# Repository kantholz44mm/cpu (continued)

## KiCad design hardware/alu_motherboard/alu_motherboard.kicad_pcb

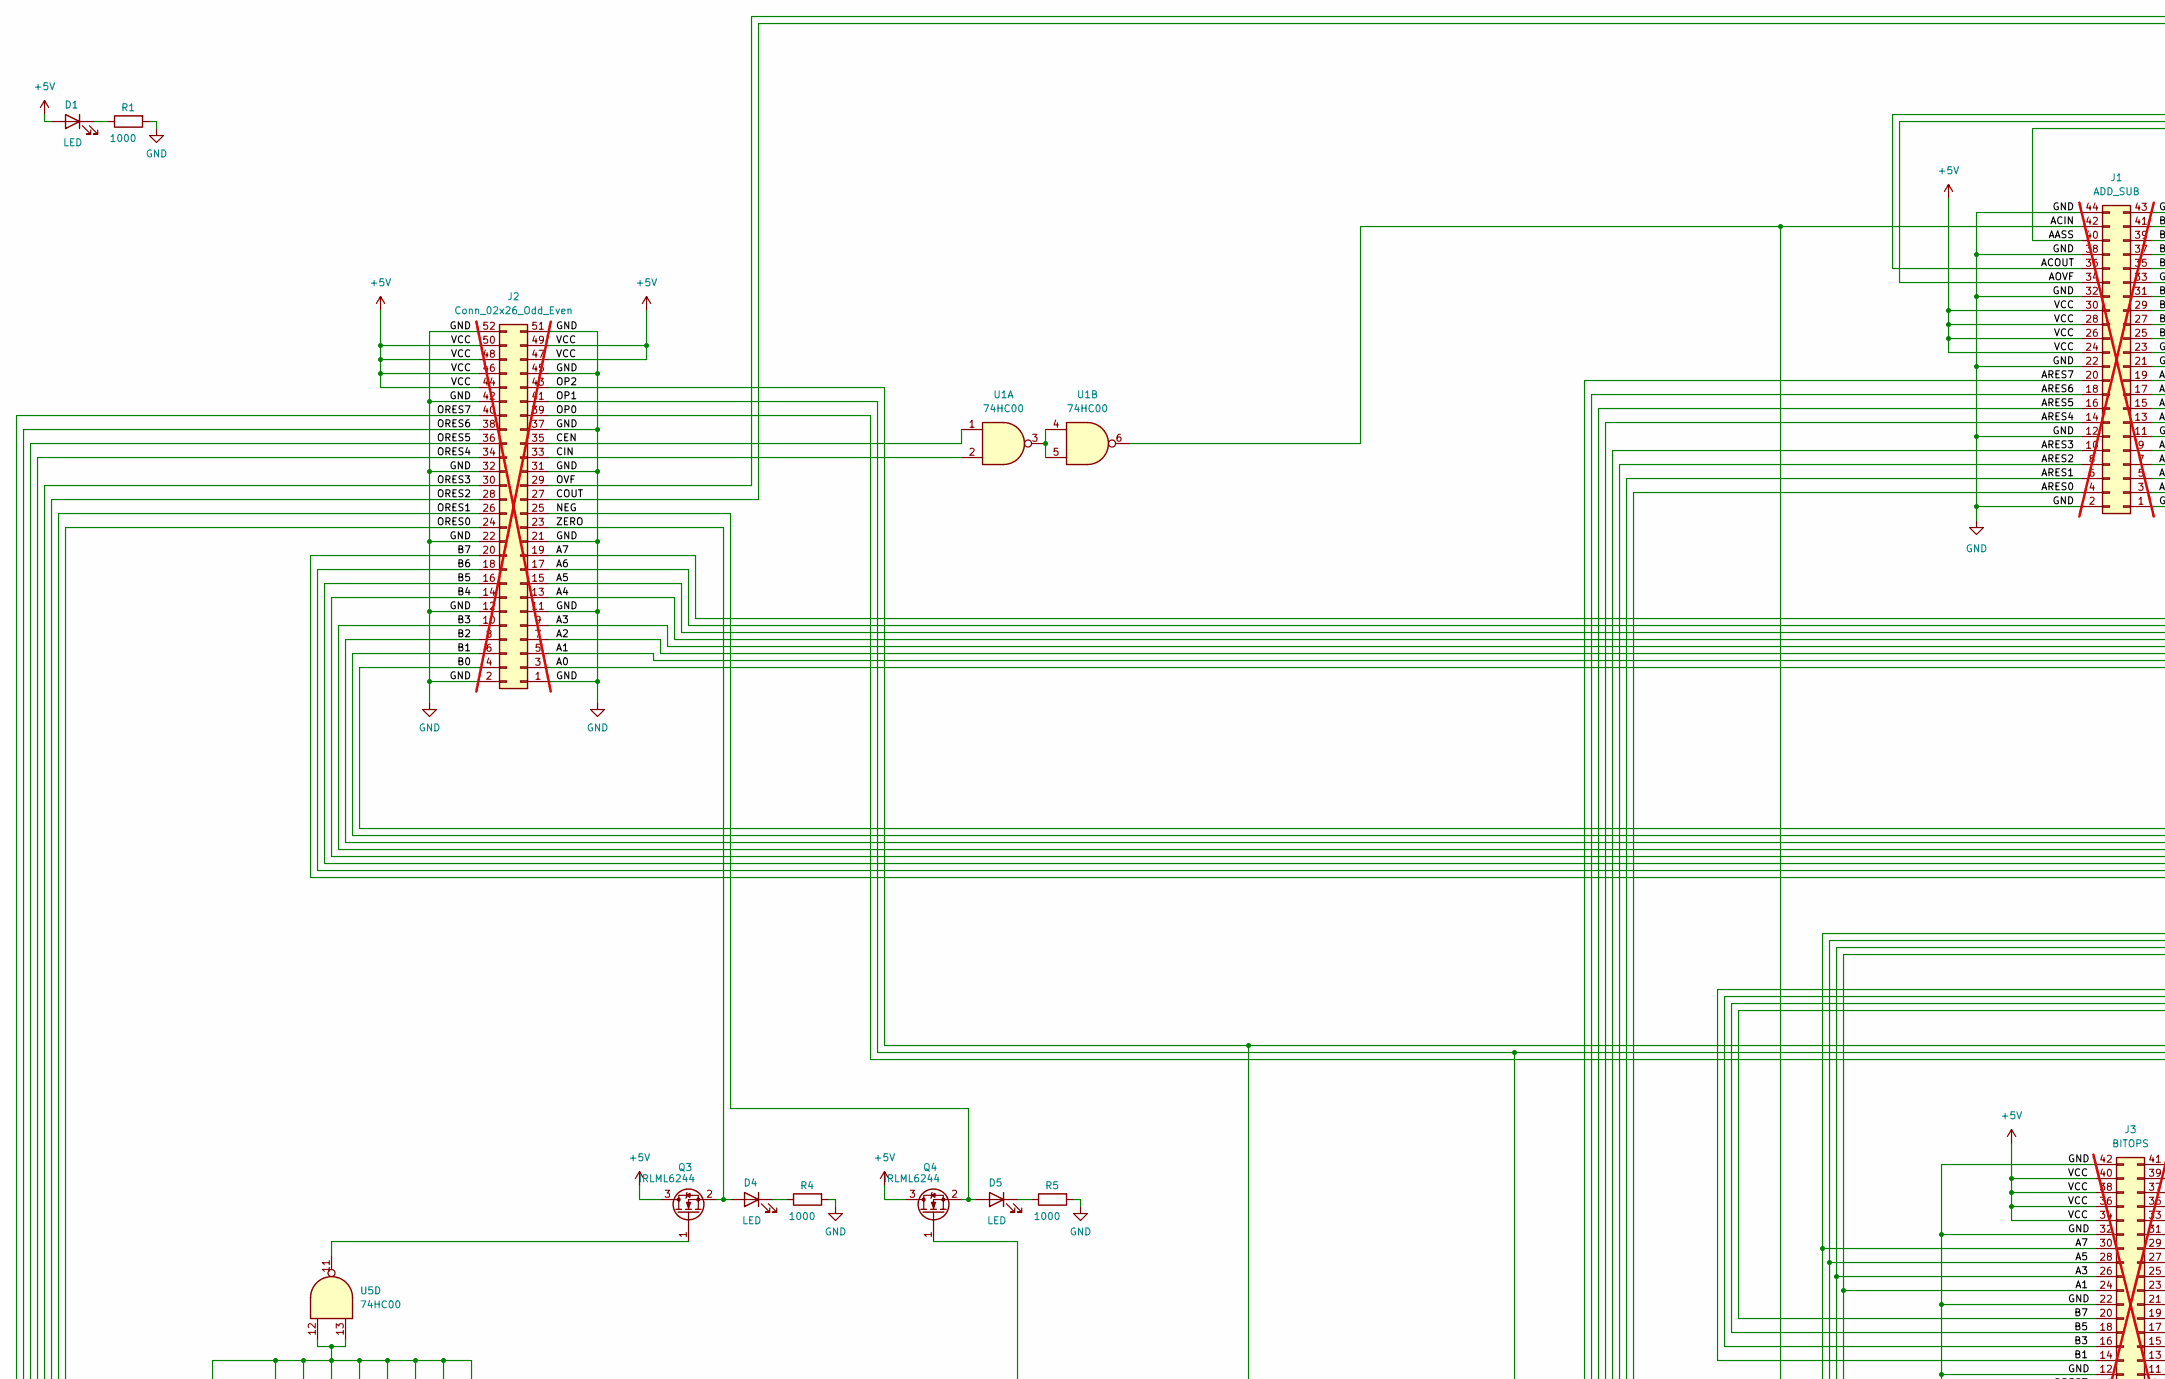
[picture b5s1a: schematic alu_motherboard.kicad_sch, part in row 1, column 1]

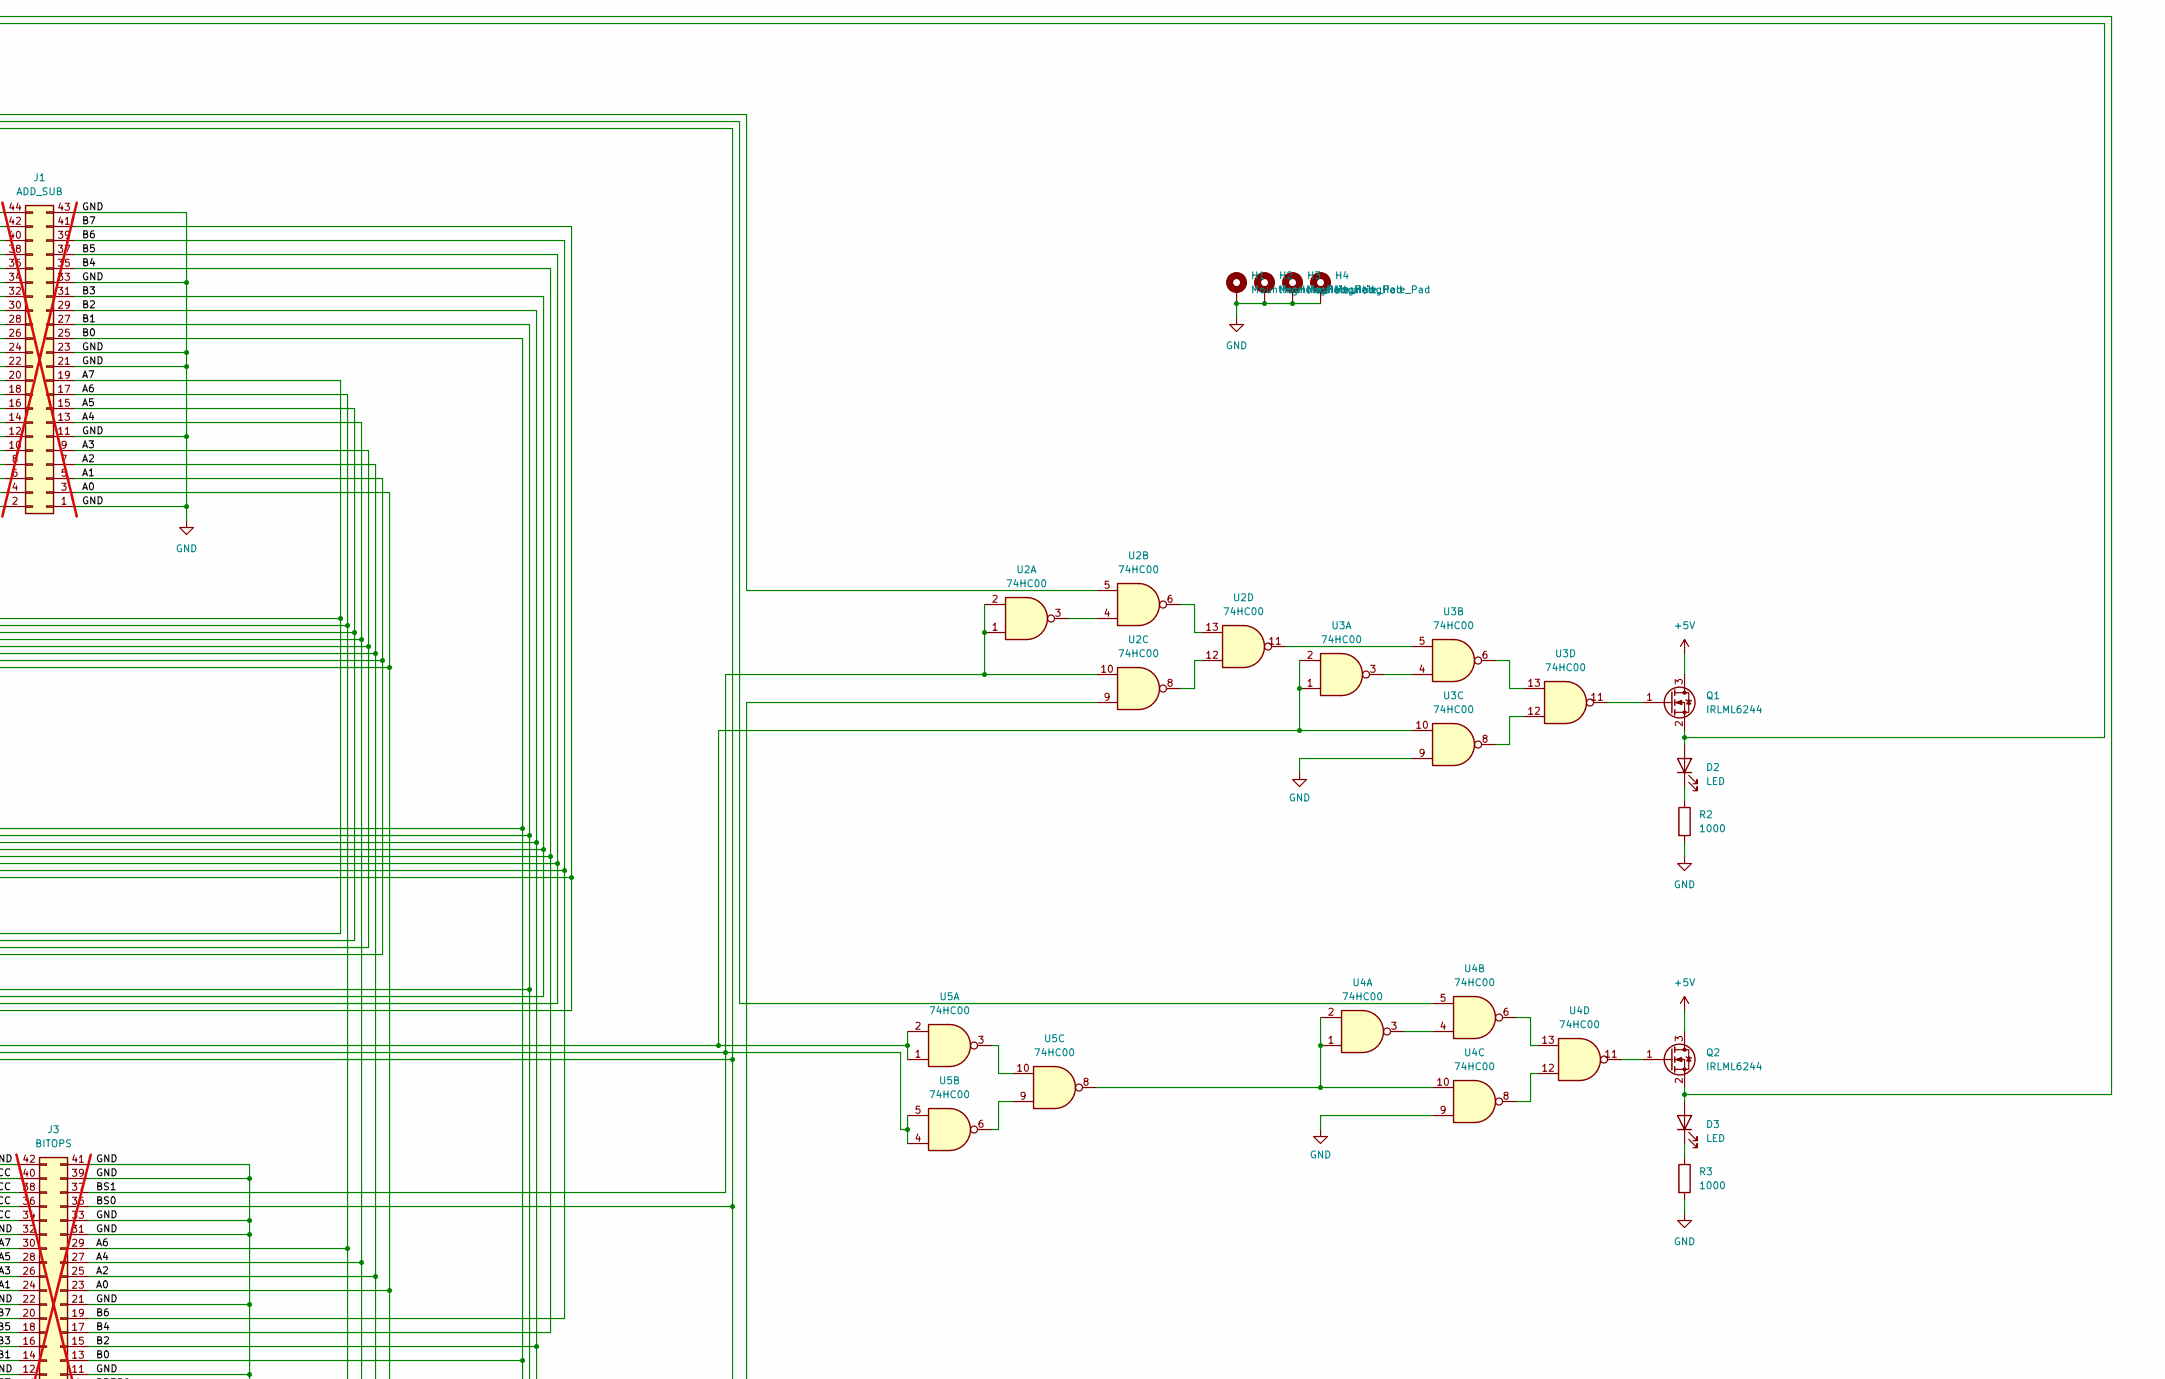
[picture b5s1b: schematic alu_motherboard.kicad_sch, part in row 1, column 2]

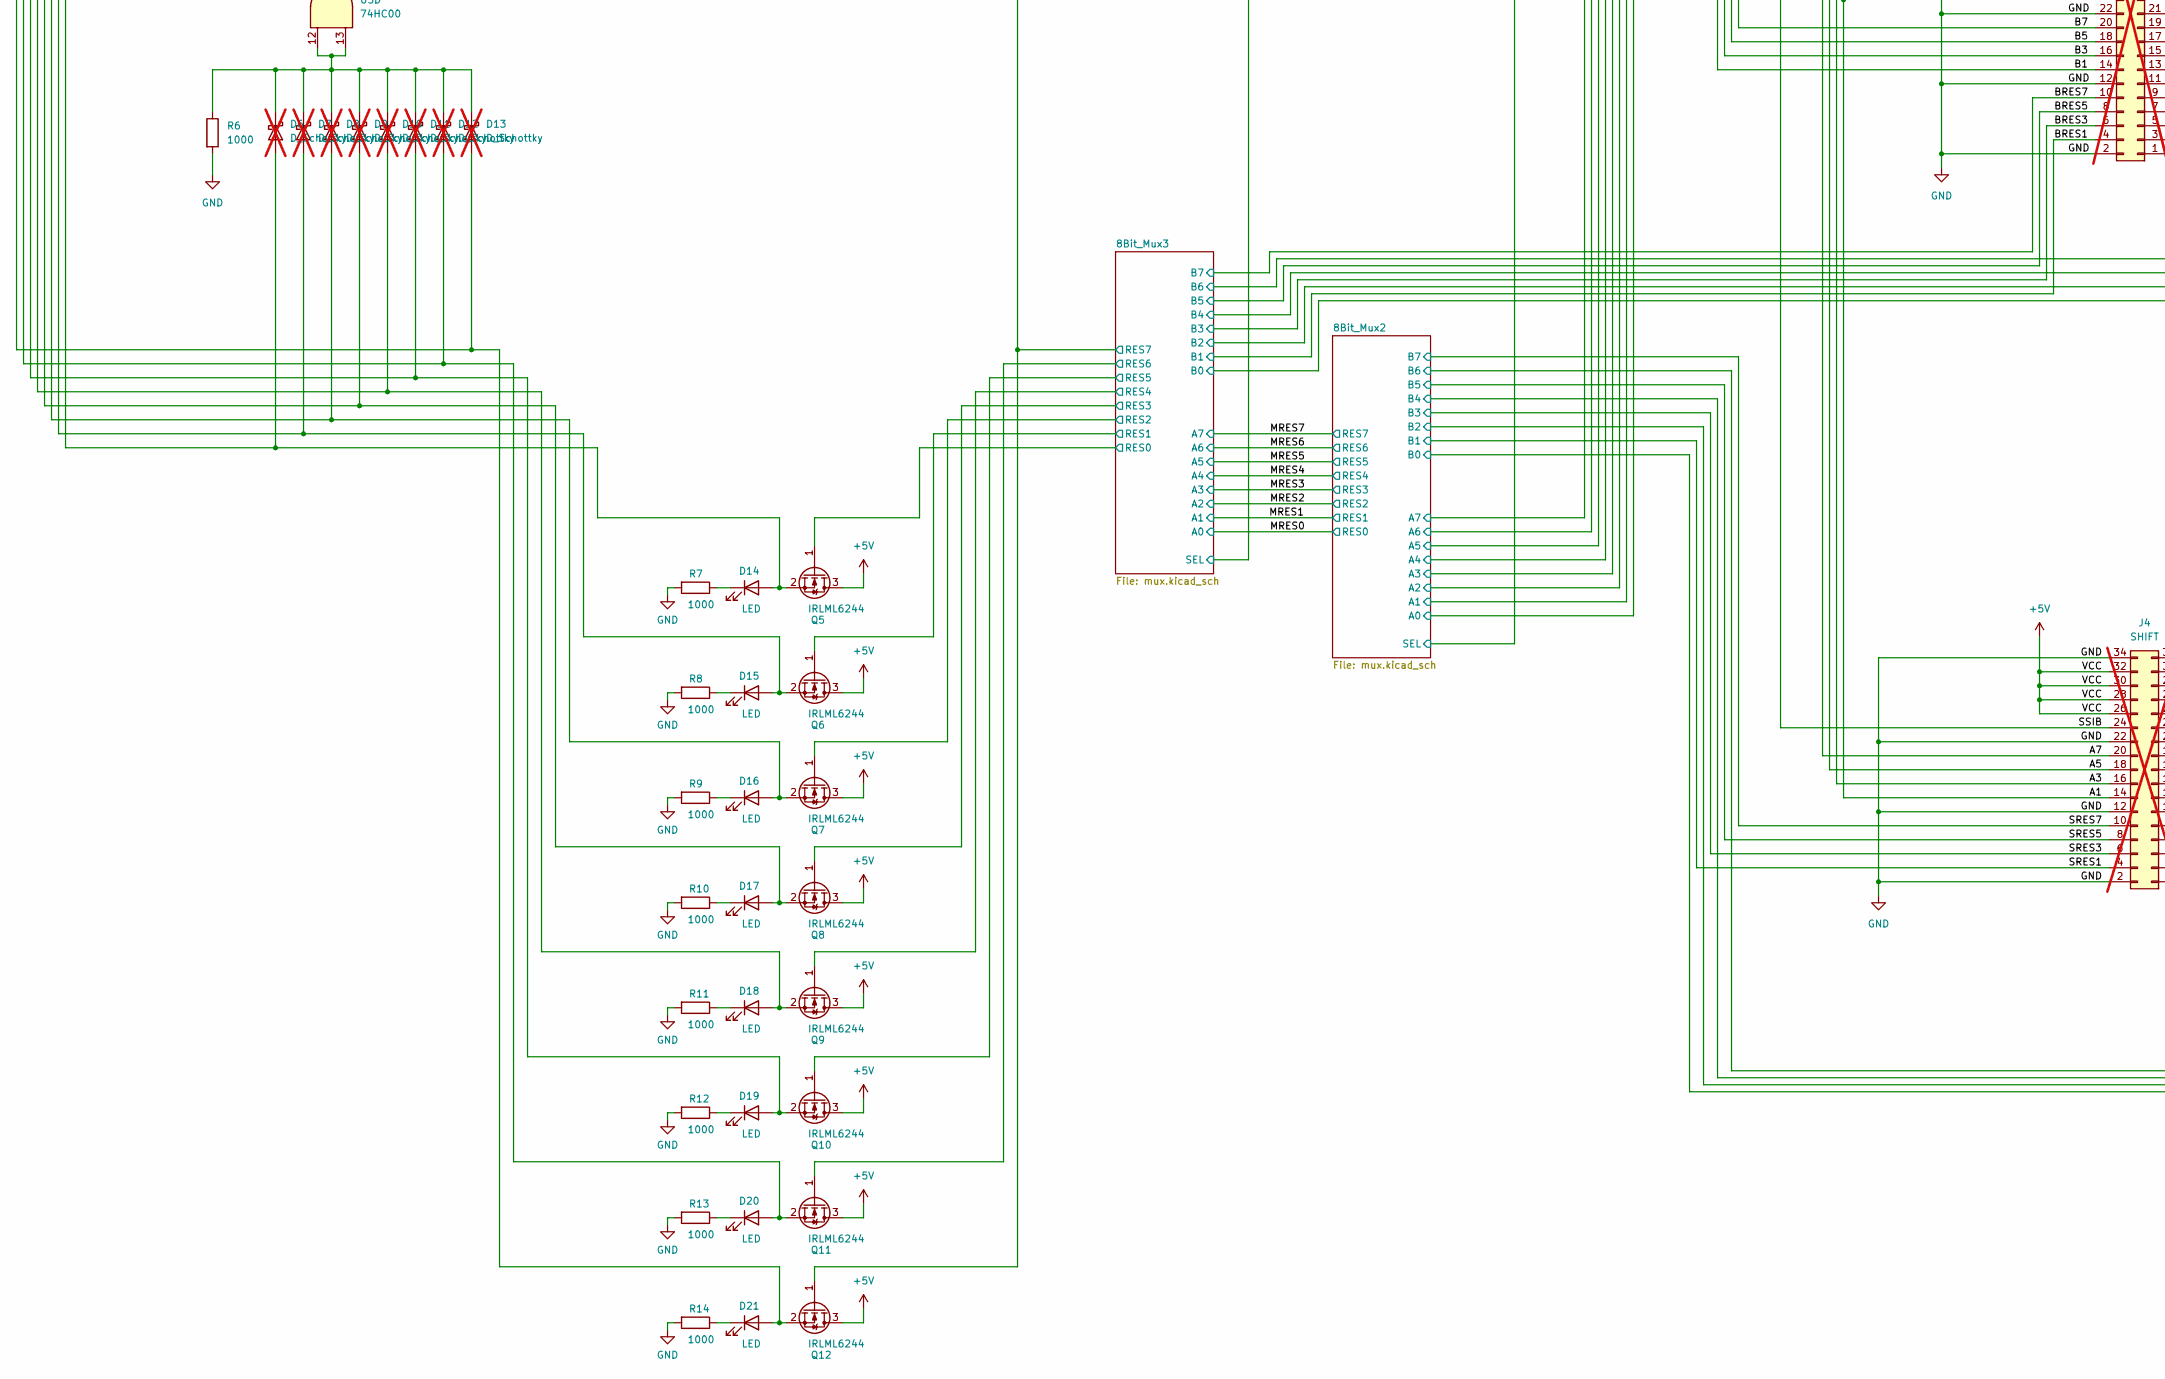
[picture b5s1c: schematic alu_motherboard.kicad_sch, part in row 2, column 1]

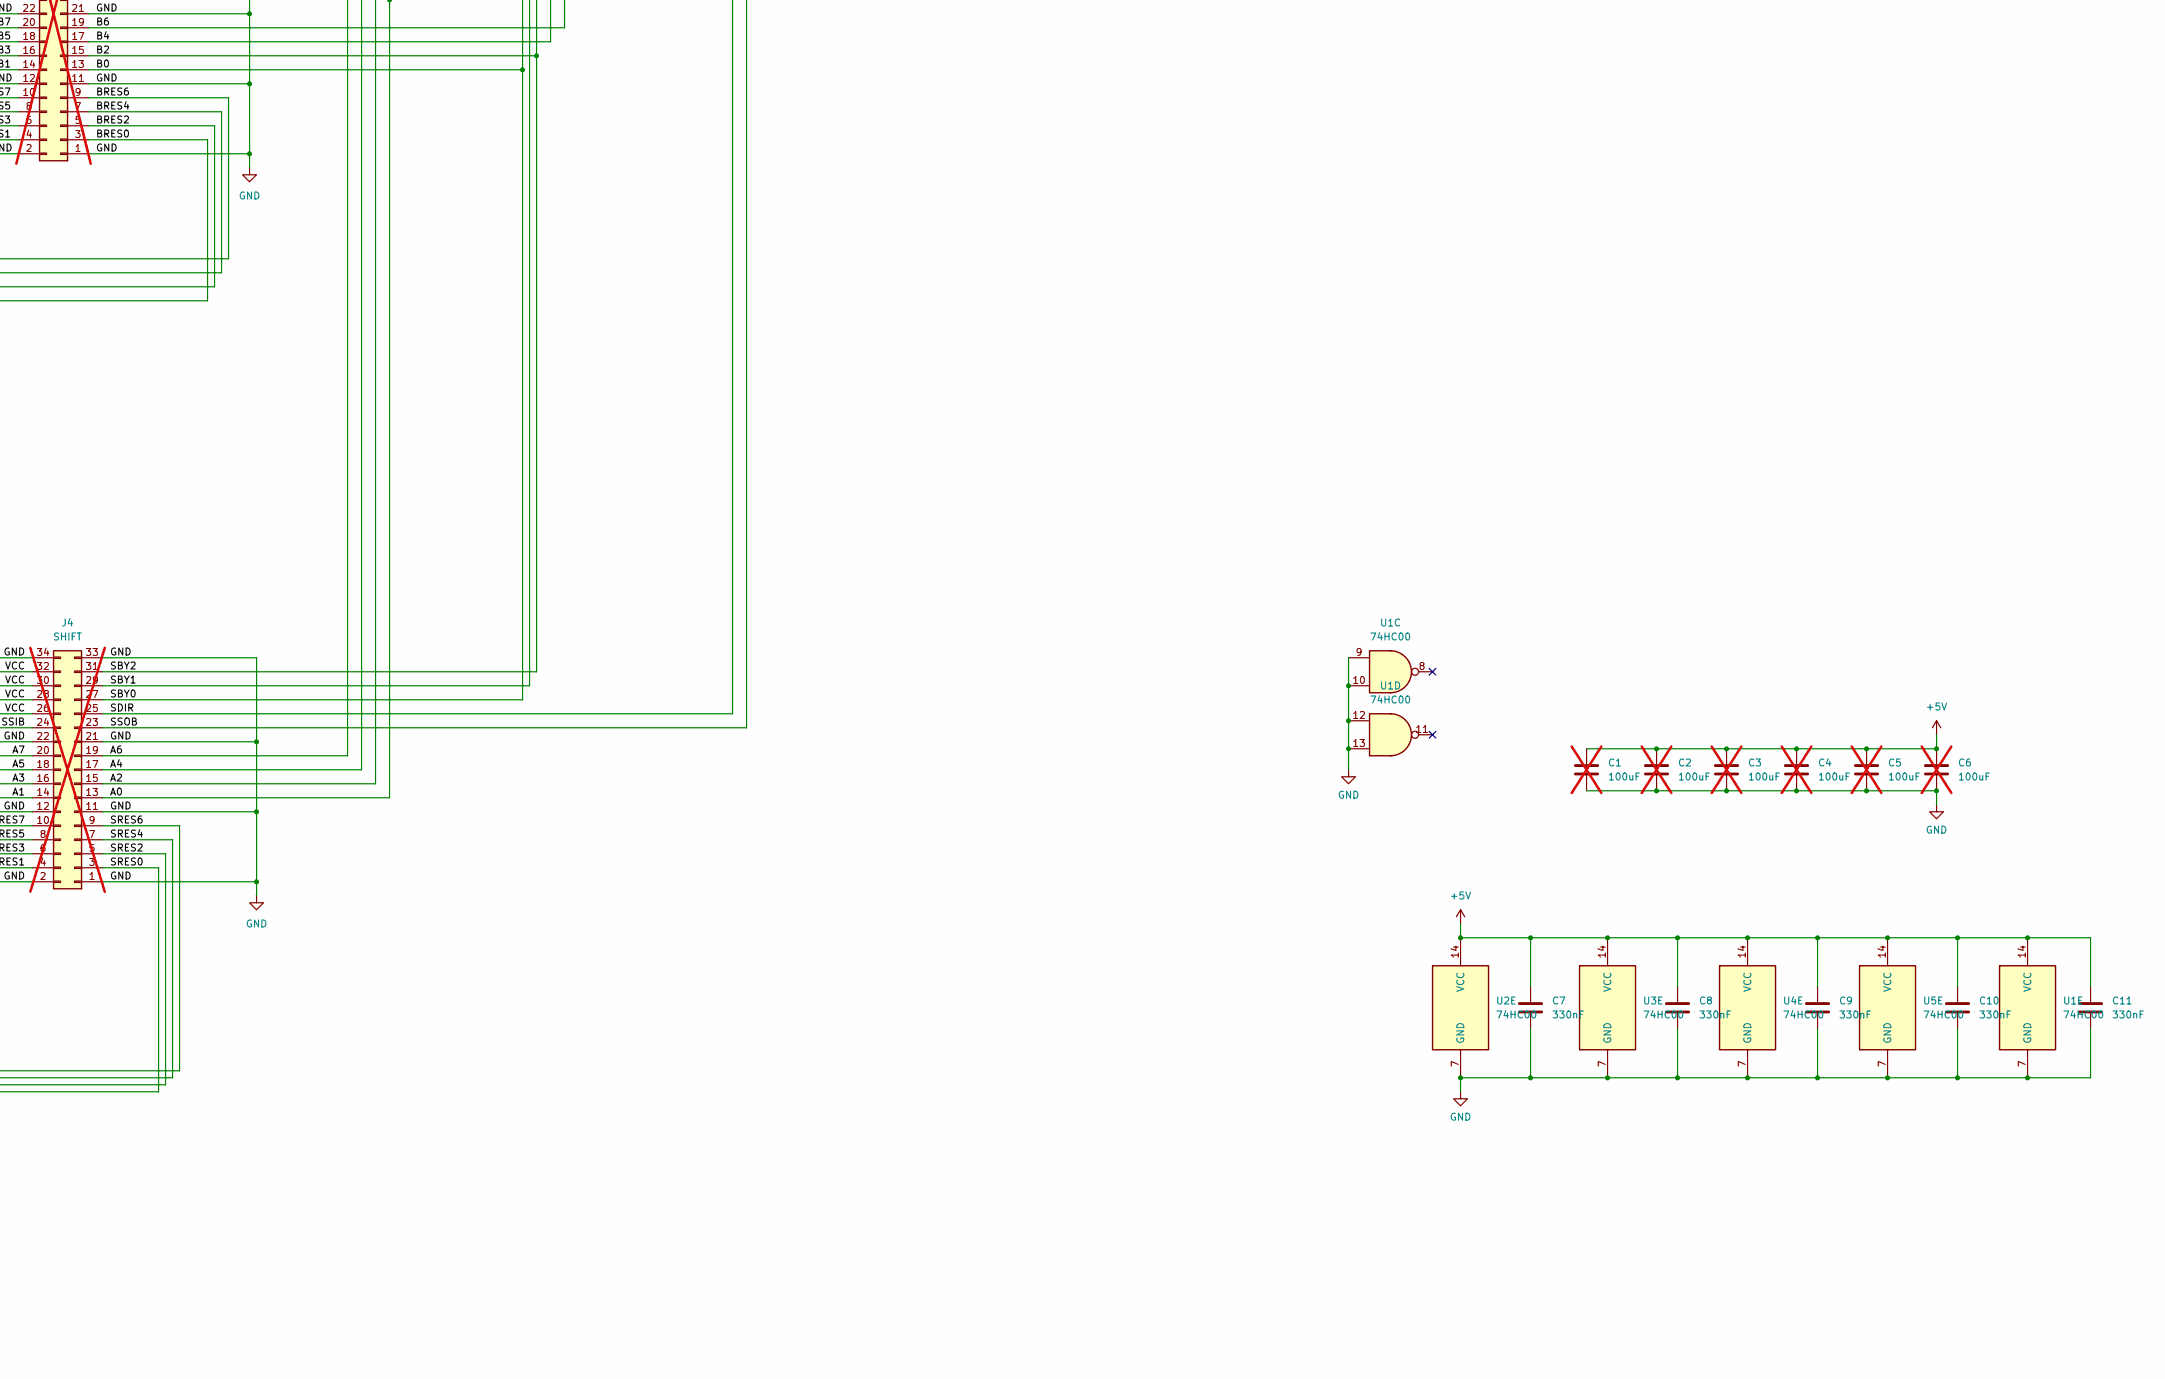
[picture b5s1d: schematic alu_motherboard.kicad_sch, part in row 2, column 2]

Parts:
C1, C2, C3, C4, C5, C6: 100uF; C_Radial_D5.0mm_H11.0mm_P2.00mm; not fitted
C7, C8, C9, C10, C11: 330nF; C_0603_1608Metric_Pad1.08x0.95mm_HandSolder; LCSC C2918485
D1, D2, D3, D4, D5, D14, D15, D16, D17, D18, D19, D20, D21: LED; LED_0603_1608Metric_Pad1.05x0.95mm_HandSolder; LCSC C84267
D6, D7, D8, D9, D10, D11, D12, D13: D_Schottky; DO35_Packed; not fitted
H1, H2, H3, H4: MountingHole_Pad; MountingHole_2.2mm_M2_Pad
J1: ADD_SUB; PinSocket_2x22_P2.54mm_Horizontal; not fitted
J2: Conn_02x26_Odd_Even; PinHeader_2x26_P2.54mm_Horizontal; not fitted
J3: BITOPS; PinSocket_2x21_P2.54mm_Horizontal; not fitted
J4: SHIFT; PinSocket_2x17_P2.54mm_Horizontal; not fitted
Q1, Q2, Q3, Q4, Q5, Q6, Q7, Q8, Q9, Q10, Q11, Q12: IRLML6244; SOT-23-3; LCSC C5123965
R1, R2, R3, R4, R5, R6, R7, R8, R9, R10, R11, R12, R13, R14: 1000; R_0603_1608Metric_Pad0.98x0.95mm_HandSolder; LCSC C21190
U1, U2, U3, U4, U5: 74HC00; SOIC-14_3.9x8.7mm_P1.27mm; LCSC C5586

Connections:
+5V: C1.1, C2.1, C3.1, C4.1, C5.1, C6.1, C7.1, C8.1, C9.1, C10.1, C11.1, D1.2 (A), J1.24, J1.26, J1.28, J1.30, J2.44, J2.46, J2.47, J2.48, J2.49, J2.50, J3.34, J3.36, J3.38, J3.40, J4.26, J4.28, J4.30, J4.32, Q1.3 (D), Q2.3 (D), Q3.3 (D), Q4.3 (D), Q5.3 (D), Q6.3 (D), Q7.3 (D), Q8.3 (D), Q9.3 (D), Q10.3 (D), Q11.3 (D), Q12.3 (D), U1.14 (VCC), U2.14 (VCC), U3.14 (VCC), U4.14 (VCC), U5.14 (VCC); also elsewhere on the board
/8Bit_Mux3/RES0: Q5.1 (G); also elsewhere on the board
/8Bit_Mux3/RES1: Q6.1 (G); also elsewhere on the board
/8Bit_Mux3/RES2: Q7.1 (G); also elsewhere on the board
/8Bit_Mux3/RES3: Q8.1 (G); also elsewhere on the board
/8Bit_Mux3/RES4: Q9.1 (G); also elsewhere on the board
/8Bit_Mux3/RES5: Q10.1 (G); also elsewhere on the board
/8Bit_Mux3/RES6: Q11.1 (G); also elsewhere on the board
/8Bit_Mux3/RES7: Q4.1 (G), Q12.1 (G); also elsewhere on the board
/A0: J1.3, J2.3, J3.23, J4.13
/A1: J1.5, J2.5, J3.24, J4.14
/A2: J1.7, J2.7, J3.25, J4.15
/A3: J1.9, J2.9, J3.26, J4.16
/A4: J1.13, J2.13, J3.27, J4.17
/A5: J1.15, J2.15, J3.28, J4.18
/A6: J1.17, J2.17, J3.29, J4.19
/A7: J1.19, J2.19, J3.30, J4.20
/AASS: J1.40, J2.39, J3.35, J4.25
/ACIN: J1.42, J4.24, U1.6
/ACOUT: J1.36, U2.5
/AOVF: J1.34, U4.5
/ARES0: J1.4; also elsewhere on the board
/ARES1: J1.6; also elsewhere on the board
/ARES2: J1.8; also elsewhere on the board
/ARES3: J1.10; also elsewhere on the board
/ARES4: J1.14; also elsewhere on the board
/ARES5: J1.16; also elsewhere on the board
/ARES6: J1.18; also elsewhere on the board
/ARES7: J1.20; also elsewhere on the board
/B0: J1.25, J2.4, J3.13, J4.27
/B1: J1.27, J2.6, J3.14, J4.29
/B2: J1.29, J2.8, J3.15, J4.31
/B3: J1.31, J2.10, J3.16
/B4: J1.35, J2.14, J3.17
/B5: J1.37, J2.16, J3.18
/B6: J1.39, J2.18, J3.19
/B7: J1.41, J2.20, J3.20
/BRES0: J3.3; also elsewhere on the board
/BRES1: J3.4; also elsewhere on the board
/BRES2: J3.5; also elsewhere on the board
/BRES3: J3.6; also elsewhere on the board
/BRES4: J3.7; also elsewhere on the board
/BRES5: J3.8; also elsewhere on the board
/BRES6: J3.9; also elsewhere on the board
/BRES7: J3.10; also elsewhere on the board
/BS1: J2.41, J3.37, U2.1, U2.2, U2.10, U5.4, U5.5; also elsewhere on the board
/CEN: J2.35, U1.1
/CIN: J2.33, U1.2
/COUT: D2.2 (A), J2.27, Q1.2 (S)
/NEG: D5.2 (A), J2.25, Q4.2 (S)
/OP2: J2.43, U3.1, U3.2, U3.10, U5.1, U5.2; also elsewhere on the board
/ORES0: D6.2 (A), D14.2 (A), J2.24, Q5.2 (S)
/ORES1: D7.2 (A), D15.2 (A), J2.26, Q6.2 (S)
/ORES2: D8.2 (A), D16.2 (A), J2.28, Q7.2 (S)
/ORES3: D9.2 (A), D17.2 (A), J2.30, Q8.2 (S)
/ORES4: D10.2 (A), D18.2 (A), J2.34, Q9.2 (S)
/ORES5: D11.2 (A), D19.2 (A), J2.36, Q10.2 (S)
/ORES6: D12.2 (A), D20.2 (A), J2.38, Q11.2 (S)
/ORES7: D13.2 (A), D21.2 (A), J2.40, Q12.2 (S)
/OVF: D3.2 (A), J2.29, Q2.2 (S)
/SRES0: J4.3; also elsewhere on the board
/SRES1: J4.4; also elsewhere on the board
/SRES2: J4.5; also elsewhere on the board
/SRES3: J4.6; also elsewhere on the board
/SRES4: J4.7; also elsewhere on the board
/SRES5: J4.8; also elsewhere on the board
/SRES6: J4.9; also elsewhere on the board
/SRES7: J4.10; also elsewhere on the board
/SSOB: J4.23, U2.9
/ZERO: D4.2 (A), J2.23, Q3.2 (S)
GND: C1.2, C2.2, C3.2, C4.2, C5.2, C6.2, C7.2, C8.2, C9.2, C10.2, C11.2, H1.1, H2.1, H3.1, H4.1, J1.1, J1.2, J1.11, J1.12, J1.21, J1.22, J1.23, J1.32, J1.33, J1.38, J1.43, J1.44, J2.1, J2.2, J2.11, J2.12, J2.21, J2.22, J2.31, J2.32, J2.37, J2.42, J2.45, J2.51, J2.52, J3.1, J3.2, J3.11, J3.12, J3.21, J3.22, J3.31, J3.32, J3.33, J3.39, J3.41, J3.42, J4.1, J4.2, J4.11, J4.12, J4.21, J4.22, J4.33, J4.34, R1.2, R2.2, R3.2, R4.2, R5.2, R6.2, R7.2, R8.2, R9.2, R10.2, R11.2, R12.2, R13.2, R14.2, U1.7 (GND), U1.9, U1.10, U1.12, U1.13, U2.7 (GND), U3.7 (GND), U3.9, U4.7 (GND), U4.9, U5.7 (GND); also elsewhere on the board
unnamed: D1.1 (K), R1.1
unnamed: D2.1 (K), R2.1
unnamed: D3.1 (K), R3.1
unnamed: D4.1 (K), R4.1
unnamed: D5.1 (K), R5.1
unnamed: D6.1 (K), D7.1 (K), D8.1 (K), D9.1 (K), D10.1 (K), D11.1 (K), D12.1 (K), D13.1 (K), R6.1, U5.12, U5.13
unnamed: D14.1 (K), R7.1
unnamed: D15.1 (K), R8.1
unnamed: D16.1 (K), R9.1
unnamed: D17.1 (K), R10.1
unnamed: D18.1 (K), R11.1
unnamed: D19.1 (K), R12.1
unnamed: D20.1 (K), R13.1
unnamed: D21.1 (K), R14.1
unnamed: Q1.1 (G), U3.11
unnamed: Q2.1 (G), U4.11
unnamed: Q3.1 (G), U5.11
unnamed: U1.3, U1.4, U1.5
unnamed: U2.3, U2.4
unnamed: U2.11, U3.5
unnamed: U2.8, U2.12
unnamed: U2.6, U2.13
unnamed: U3.3, U3.4
unnamed: U3.8, U3.12
unnamed: U3.6, U3.13
unnamed: U4.1, U4.2, U4.10, U5.8
unnamed: U4.3, U4.4
unnamed: U4.8, U4.12
unnamed: U4.6, U4.13
unnamed: U5.6, U5.9
unnamed: U5.3, U5.10
